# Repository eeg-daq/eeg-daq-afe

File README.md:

# eeg-daq-afe
Carte Front-End Analogique (AFE) d'acquisition EEG basée sur l'ADS1299

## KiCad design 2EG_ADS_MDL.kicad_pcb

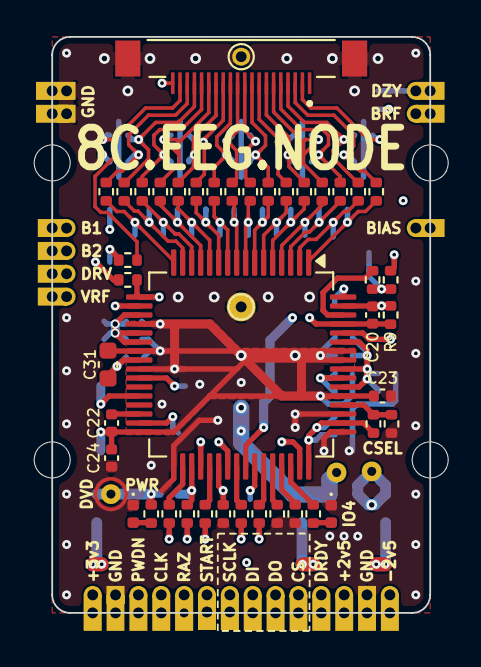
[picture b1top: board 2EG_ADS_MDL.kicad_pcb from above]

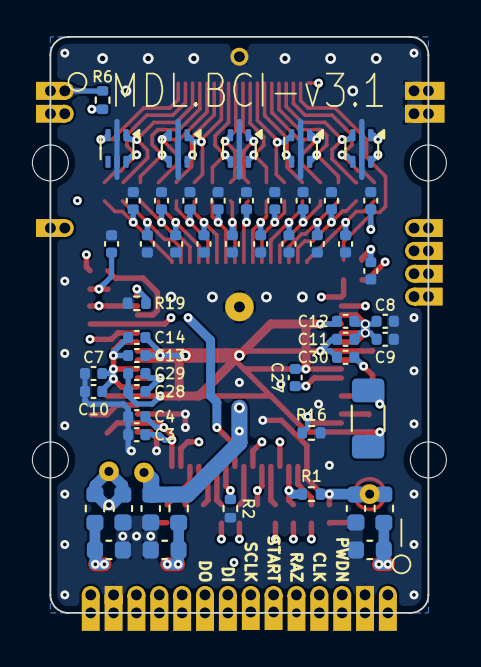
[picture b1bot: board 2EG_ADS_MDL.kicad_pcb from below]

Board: 4 copper layers, 21.0 x 32.0 mm, 126 parts (56 on the bottom side), 78 nets.

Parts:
C1, C2, C5, C6, C25, C26, C31: 10uF; C_0603_1608Metric
C3, C7, C8, C11, C12, C22, C24, C27, C29: 1uF; C_0402_1005Metric
C4, C9, C10, C13, C14, C23, C28, C30: 100nF; C_0402_1005Metric
C20: 1.5nF; C_0402_1005Metric
C21: 100uF; C_1206_3216Metric_Pad1.33x1.80mm_HandSolder
C32, C33, C34, C35, C36, C37, C38, C39, C40, C41, C42, C43, C44, C45, C46, C47, C48, C49, C50: 4.7nF; C_0402_1005Metric
D1, D2, D3, D4, D5: TPD4E1B06; Texas_R-PDSO-N6_DRL-6
D6: Blue; D_0402_1005Metric
D7: Green; D_0402_1005Metric
J1: 20374-R20E-31; I-PEX_20374-R20E-31
J2: Conn_01x01_Pin; PinHeader_1x04_P1.27mm_Vertical
J3: Conn_01x14_Pin; PinHeader_1x14_P1.27mm_Vertical
J4: Conn_01x01_Pin; PinHeader_1x02_P1.27mm_Vertical
L1, L2, L3: 600Ω_100 MHz; L_0603_1608Metric
R1, R5, R18: 10k; R_0402_1005Metric
R2, R3, R4, R15, R19: 100k; R_0402_1005Metric
R6, R7, R8, R11, R12, R13, R14, R16: 50Ω; R_0402_1005Metric
R9: 1M; R_0402_1005Metric
R10: 0Ω; R_0402_1005Metric
R17: DNP; R_0402_1005Metric
R20, R21, R22, R23, R24, R25, R26, R27, R28, R29, R30, R31, R32, R33, R34, R35, R36, R37, R38: 4k99; R_0402_1005Metric
TP1: DVD; TestPoint_Pad_D1.0mm
TP2: AVD; TestPoint_THTPad_D1.0mm_Drill0.5mm
TP3: AVS; TestPoint_THTPad_D1.0mm_Drill0.5mm
TP4: AGND; TestPoint_THTPad_D1.0mm_Drill0.5mm
TP4#2, TP4#3, TP4#4, TP4#5, TP4#6, TP4#7, TP4#8, TP4#9, TP4#10, TP4#11, TP4#12, TP4#13, TP4#14, TP4#16, TP4#18, TP4#19, TP4#20, TP4#23, TP4#24, TP4#25: GND; Edge_Weld
TP4#15, TP4#17, TP4#22: GND; TestPoint_THTPad_D1.0mm_Drill0.5mm
TP4#21: AGND; Edge_Weld
U1: ADS1299; TQFP-64_10x10mm_P0.5mm

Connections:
+2V5: C5.1, J3.12, L2.2, TP4#2.1
+3V3: C1.1, J3.1, L1.1, TP4#15.1
-2V5: C26.1, J3.14, L3.2, TP4#7.1
/1N: C35.1, R23.1, U1.15 (IN1N)
/1P: C34.1, R22.1, U1.16 (IN1P)
/2N: C37.1, R25.1, U1.13 (IN2N)
/2P: C36.1, R24.1, U1.14 (IN2P)
/3N: C39.1, R27.1, U1.11 (IN3N)
/3P: C38.1, R26.1, U1.12 (IN3P)
/4N: C41.1, R29.1, U1.9 (IN4N)
/4P: C40.1, R28.1, U1.10 (IN4P)
/5N: C43.1, R31.1, U1.7 (IN5N)
/5P: C42.1, R30.1, U1.8 (IN5P)
/6N: C45.1, R33.1, U1.5 (IN6N)
/6P: C44.1, R32.1, U1.6 (IN6P)
/7N: C47.1, R35.1, U1.3 (IN7N)
/7P: C46.1, R34.1, U1.4 (IN7P)
/8N: C49.1, R37.1, U1.1 (IN8N)
/8P: C48.1, R36.1, U1.2 (IN8P)
/B0: C20.1, C50.1, R9.2, R10.2, R38.1, U1.63 (RLDOUT)
/B1: C32.1, J2.4, R20.1, TP4#13.1, U1.17 (SRB1)
/B2: C33.1, J2.3, R21.1, TP4#12.1, U1.18 (SRB2)
/BIAS: D5.3 (TVS2), J1.2, R38.2, TP4#25.1
/BIASI: R10.1, U1.62 (RLDIN)
/B_REF: J4.2, TP4#3.1, U1.60 (RLDREF)
/CLKSEL: R14.1, R17.2, U1.52 (CLKSEL)
/CS: J3.10, TP4#8.1, U1.39 (~CS)
/DAISY: J4.1, R6.1, TP4#4.1
/DRDY: J3.11, TP4#10.1, U1.47 (~DRDY)
/IN1N: D1.3 (TVS2), J1.17, R23.2
/IN1P: D1.4 (TVS3), J1.18, R22.2
/IN2N: D2.1 (TVS1), J1.15, R25.2
/IN2P: D2.6 (TVS4), J1.16, R24.2
/IN3N: D2.3 (TVS2), J1.13, R27.2
/IN3P: D2.4 (TVS3), J1.14, R26.2
/IN4N: D3.1 (TVS1), J1.11, R29.2
/IN4P: D3.6 (TVS4), J1.12, R28.2
/IN5N: D3.4 (TVS3), J1.9, R31.2
/IN5P: D3.3 (TVS2), J1.10, R30.2
/IN6N: D4.6 (TVS4), J1.7, R33.2
/IN6P: D4.1 (TVS1), J1.8, R32.2
/IN7N: D4.4 (TVS3), J1.5, R35.2
/IN7P: D4.3 (TVS2), J1.6, R34.2
/IN8N: D5.6 (TVS4), J1.3, R37.2
/IN8P: D5.1 (TVS1), J1.4, R36.2
/PWDN: J3.3, R13.2, TP4#11.1
/SRB1: D1.6 (TVS4), J1.20, R20.2
/SRB2: D1.1 (TVS1), J1.19, R21.2
/START: J3.6, R15.2, TP4#20.1, U1.38 (START)
/VREF: C30.1, C31.1, J2.1, TP4#18.1, U1.24 (VREFP)
ADS_CLK: J3.4, R12.2, TP4#6.1
ADS_RST: J3.5, TP4.1 (1_1), U1.36 (~RESET)
AGND: C1.2, C2.2, C3.2, C4.2, C5.2, C6.2, C7.2, C8.2, C9.2, C10.2, C23.2, C24.2, C25.2, C26.2, C32.2, C33.2, C34.2, C35.2, C36.2, C37.2, C38.2, C39.2, C40.2, C41.2, C42.2, C43.2, C44.2, C45.2, C46.2, C47.2, C48.2, C49.2, C50.2, D1.2 (COM), D1.5 (COM), D2.2 (COM), D2.5 (COM), D3.2 (COM), D3.5 (COM), D4.2 (COM), D4.5 (COM), D5.2 (COM), D5.5 (COM), D6.1 (K), D7.1 (K), J1.S1 (MountPin), J1.S2 (MountPin), J3.2, J3.13, R2.1, R3.1, R4.1, R14.2, R15.1, R16.2, R19.1, TP4#5.1, TP4#16.1, TP4#17.1, TP4#22.1, TP4#23.1, TP4#24.1, U1.33 (DGND), U1.49 (DGND), U1.51 (DGND)
AVDD: C6.1, C7.1, C8.1, C9.1, C10.1, C11.1, C12.1, C13.1, C14.1, L2.1, TP2.1 (1_1), U1.19 (AVDD), U1.21 (AVDD), U1.22 (AVDD), U1.54 (AVDD1), U1.56 (AVDD), U1.59 (AVDD)
AVSS: C11.2, C12.2, C13.2, C14.2, C21.2, C22.2, C23.1, C24.1, C25.1, C27.2, C28.2, C29.2, C30.2, C31.2, L3.1, TP3.1 (1_1), U1.20 (AVSS), U1.23 (AVSS), U1.25 (VREFN), U1.32 (AVSS), U1.53 (AVSS1), U1.57 (AVSS), U1.58 (AVSS)
BIAS_DRV: C20.2, J2.2, R9.1, TP4#21.1 (1_1), U1.61 (RLDINV)
DVDD: C2.1, C3.1, C4.1, L1.2, R1.2, R17.1, R18.2, TP1.1 (1_1), U1.48 (DVDD), U1.50 (DVDD)
MISO: J3.9, R11.2, TP4#19.1
MOSI: J3.8, R8.2, TP4#14.1
unnamed: D6.2 (A), R5.1
unnamed: D7.2 (A), R18.1
unnamed: R12.1, U1.37 (CLK)
unnamed: R6.2, U1.41 (DAISY_IN)
unnamed: R8.1, U1.34 (DIN)
unnamed: R11.1, U1.43 (DOUT)
unnamed: R2.2, U1.42 (GPIO1)
unnamed: R4.2, U1.44 (GPIO2)
unnamed: R3.2, U1.45 (GPIO3)
unnamed: R5.2, U1.46 (GPIO4)
unnamed: R16.1, U1.31 (RESV1)
unnamed: R19.2, U1.64 (Reserved)
unnamed: R7.1, U1.40 (SCLK)
unnamed: C21.1, U1.28 (VCAP1)
unnamed: C22.1, U1.30 (VCAP2)
unnamed: C28.1, C29.1, U1.55 (VCAP3)
unnamed: C27.1, U1.26 (VCAP4)
unnamed: R1.1, R13.1, U1.35 (~PWDN)
SCLK: J3.7, R7.2, TP4#9.1
